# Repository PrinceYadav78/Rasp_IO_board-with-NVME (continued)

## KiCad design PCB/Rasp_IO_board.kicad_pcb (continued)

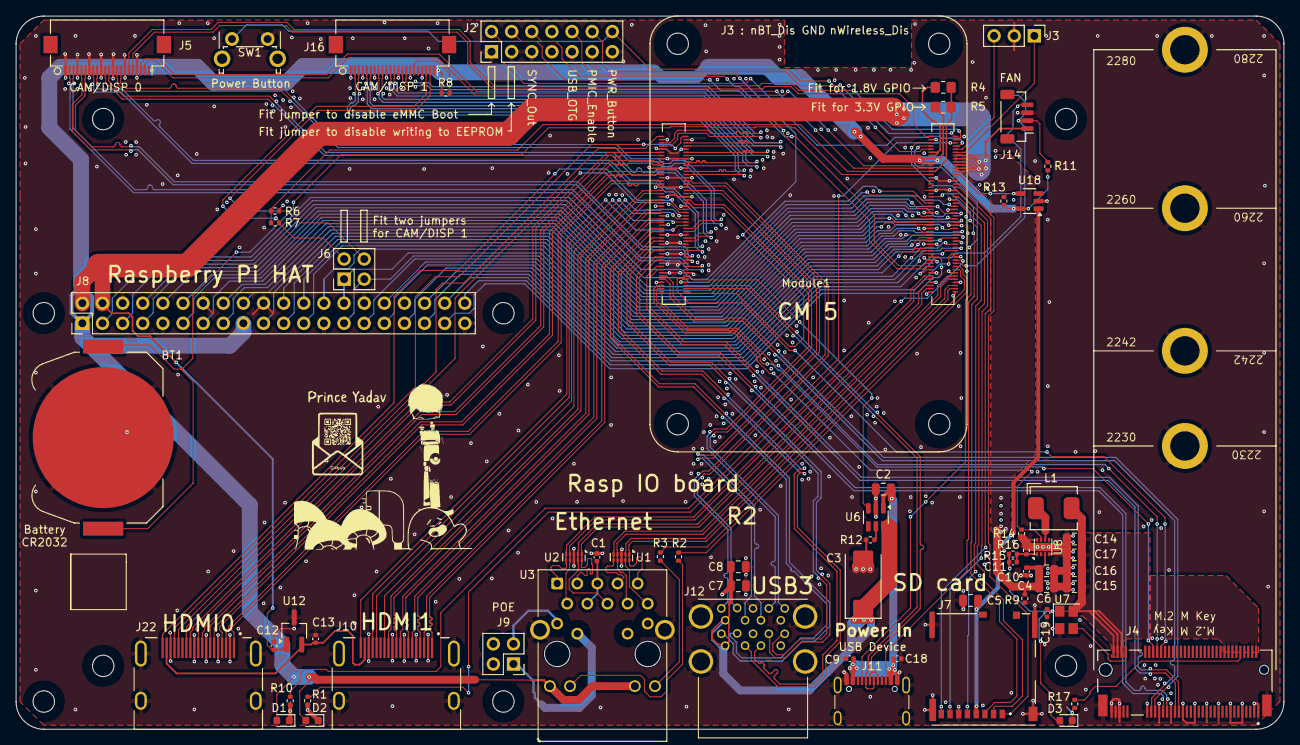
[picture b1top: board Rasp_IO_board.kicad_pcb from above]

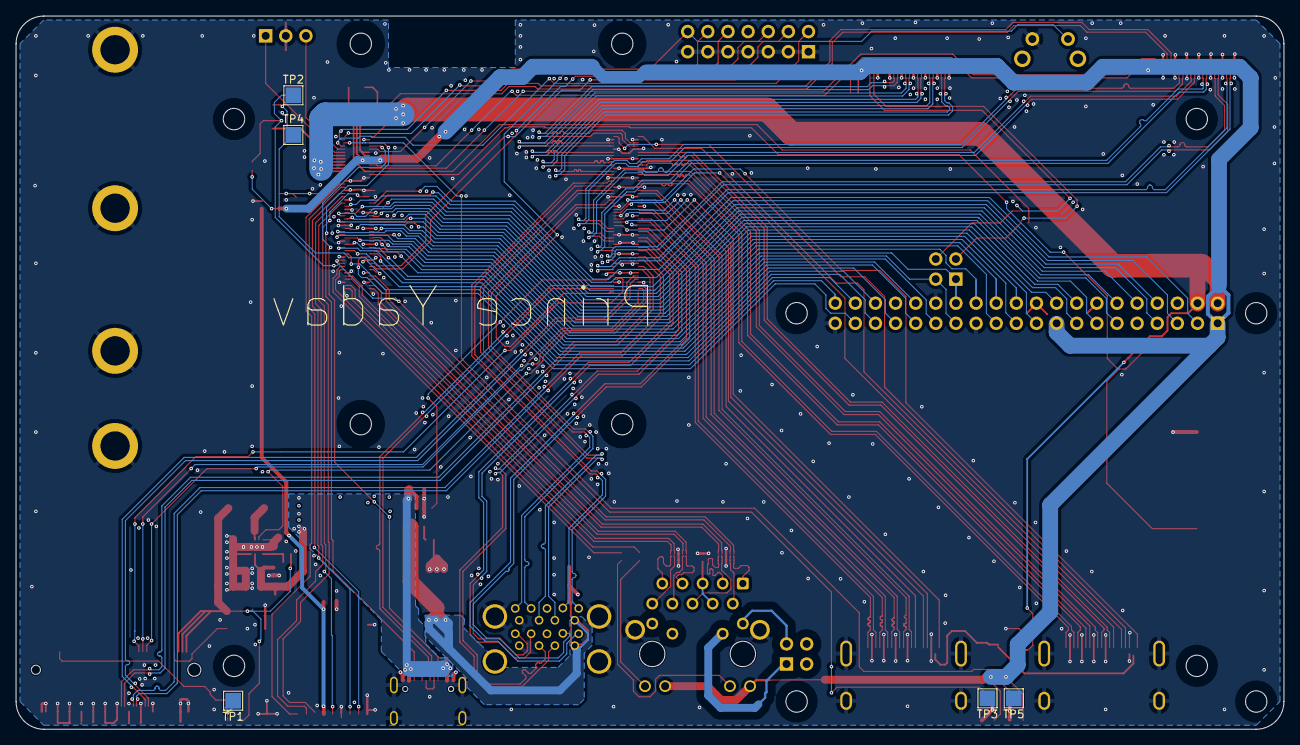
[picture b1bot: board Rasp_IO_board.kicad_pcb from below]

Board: 4 copper layers, 160.0 x 90.0 mm, 78 parts (5 on the bottom side), 160 nets.

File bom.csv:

Designator,Footprint,Quantity,Value,LCSC Part #
BT1,BatteryHolder_Keystone_3034_1x20mm,1,Battery_Cell,
"C1, C10, C12, C13, C18, C19, C9",0402,7,100n,
C11,0402,1,4.7nF,
"C14, C15, C16, C17, C2, C4, C5, C6, C7, C8",0805,10,10u,
C3,CP_EIA-7343-31_Kemet-D,1,100uF,
D1,0603,1,LED Red,
"D2, D3",0603,2,LED Green,
"J10, J22",EDAC 690-019-298-412,2,690-019-298-412,
J11,USB_C_Receptacle_GCT_USB4105-xx-A_16P_TopMnt_Horizontal,1,USB_C_Receptacle_USB2.0,
J12,MTCONN_UBAF30-D2011,1,USB3_A,
J14,JST_SH_BM04B-SRSS-TB_1x04-1MP_P1.00mm_Vertical,1,JST_SHBM04B-SRSS-TB,
"J16, J5",Hirose_FH12-22S-0.5SH_1x22-1MP_P0.50mm_Horizontal,2,Conn_01x22_Female,
J2,PinHeader_2x07_P2.54mm_Vertical,1,Conn_02x07_Odd_Even,
J4,M.2 M Key socket,1,Bus_M.2_Socket_M,
"J6, J9",PinHeader_2x02_P2.54mm_Vertical,2,THD-02-R,
J7,SDCARD_MOLEX_503398-1892,1,Micro_SD_Card_Det,
J8,PinHeader_2x20_P2.54mm_Vertical,1,THD-20-R,
L1,L_Bourns_SRP5030CC,1,2.2uH,
MODULE1,Raspberry-Pi-5-Compute-Module,1,ComputeModule5-CM5,
"R1, R10, R17",0402,3,1k,
"R11, R13, R15",0402,3,10K 1%,
R12,0402,1,15K 1%,
R14,0402,1,100K 1%,
"R16, R6, R7, R8, R9",0402,5,2.2K 1%,
"R2, R3",0402,2,470R,
R5,0805,1,0R,
SW1,SW_Tactile_SPST_Angled_PTS645Vx58-2LFS,1,Right angle Tact button,
"U1, U2",USON-10_2.5x1.0mm_P0.5mm,2,TPD4EUSB30,
U12,TSOT-23_HandSoldering,1,RT9742SNGV,
U18,SOT-23-5,1,RT9742GGJ5,
U3,TRJG0926HENL,1,MagJack-A70-112-331N126,
U6,SOT-23-6,1,AP22653W6,
U7,Crystal_SMD_3225-4Pin_3.2x2.5mm,1,ASEK-32.768KHZ-L-R-T,
U8,DFN-8-1EP_2x2mm_P0.5mm_EP1.05x1.75mm,1,AP3441SHE-7B,
